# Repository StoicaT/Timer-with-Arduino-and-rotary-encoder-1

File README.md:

# Timer-with-rotary-encoder 
This countdown timer allows timings in the 1-9999 seconds range.
It is built around an Arduino Nano and timer programming is done with a rotary encoder.
The display of the duration of the delay and the remaining time is made with LCD display type 1602.

Programming:  Set number seconds (rotary encoder) - push - secondsX10 - push - 100Xseconds - push - 1000Xseconds
Now the time is set.
The next push will trigger the delay.

During the time delay the load will be powered through the Rel relay.
If the MEM button is pressed, no further programming is required, the previous value is retained.
More to https://www.instructables.com/id/Timer-With-Arduino-and-Rotary-Encoder/

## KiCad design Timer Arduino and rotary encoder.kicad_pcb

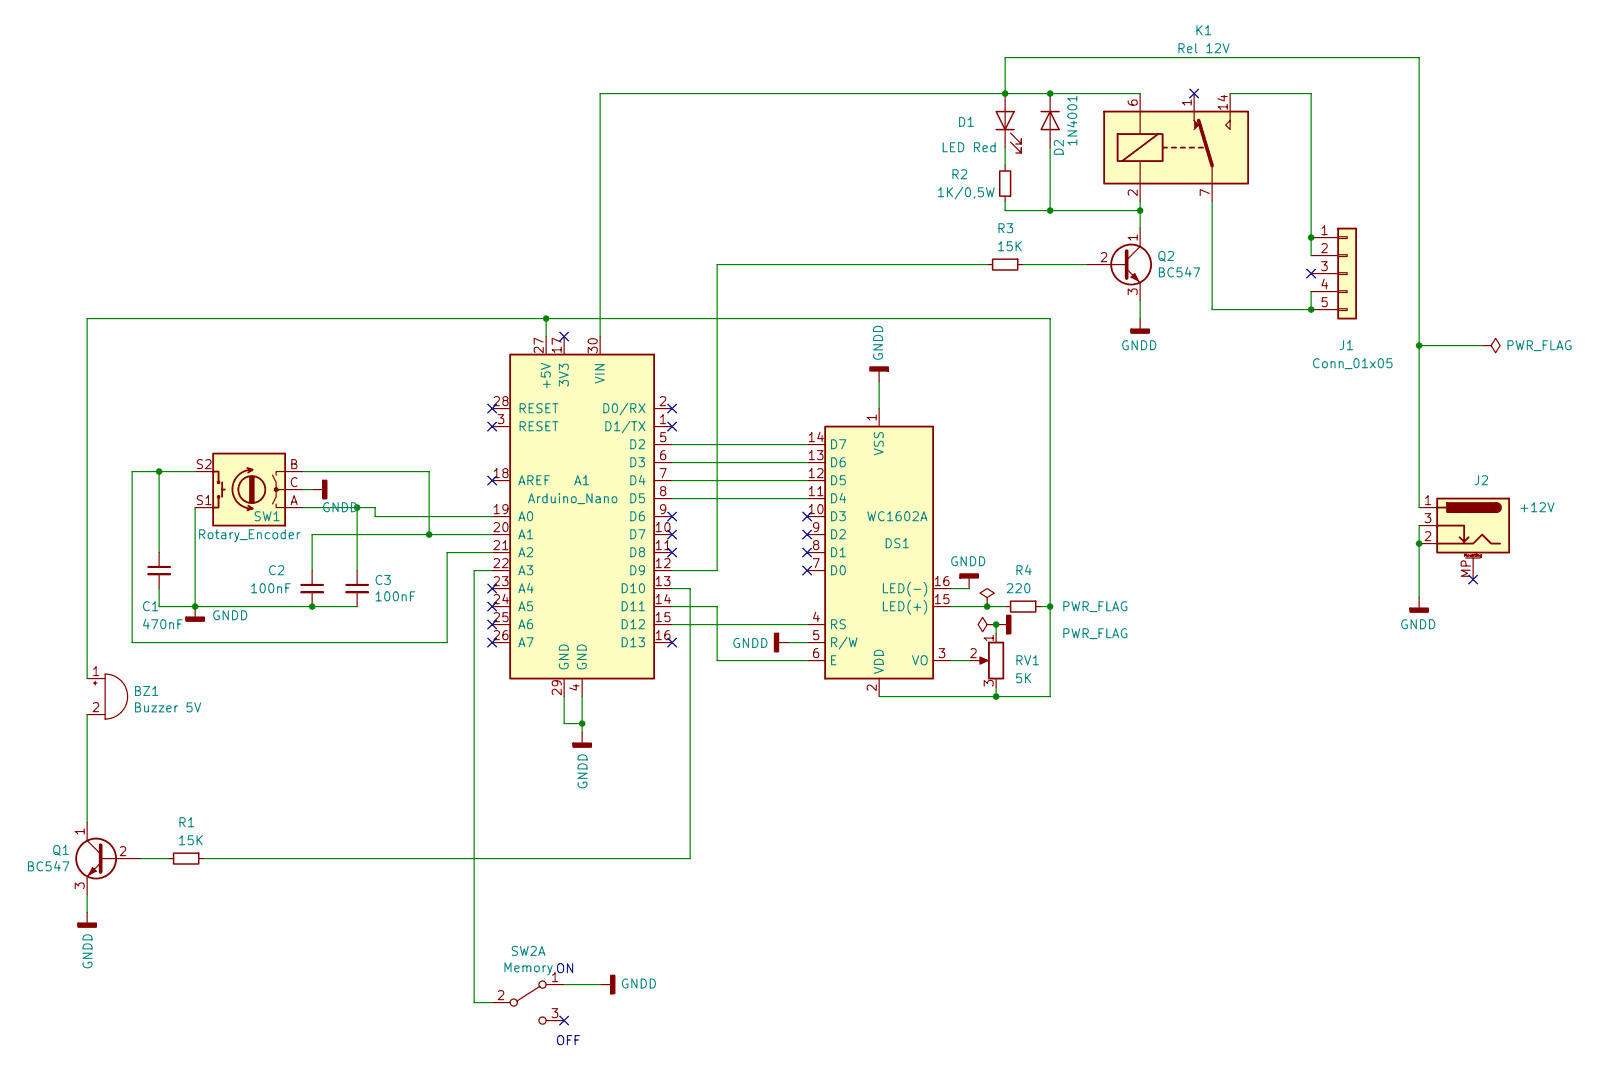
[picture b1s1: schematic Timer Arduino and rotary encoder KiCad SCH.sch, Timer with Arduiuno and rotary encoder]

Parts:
A1: Arduino_Nano; Arduino_Nano_WithMountingHoles
BZ1: Buzzer 5V; Buzzer_12x9.5RM7.6
C1: 470nF; C_Rect_L7.0mm_W2.0mm_P5.00mm
C2, C3: 100nF; C_Rect_L7.0mm_W2.0mm_P5.00mm
D1: LED Red; LED_D5.0mm
D2: 1N4001; D_DO-41_SOD81_P10.16mm_Horizontal
DS1: WC1602A
J1: Conn_01x05; PinHeader_1x05_P2.54mm_Horizontal
J2: +12V; BarrelJack_Horizontal
K1: Rel 12V
Q1, Q2: BC547; TO-92_Inline
R1, R3: 15K; R_Axial_DIN0207_L6.3mm_D2.5mm_P10.16mm_Horizontal
R2: 1K/0,5W; R_Axial_DIN0309_L9.0mm_D3.2mm_P12.70mm_Horizontal
R4: 220; R_Axial_DIN0207_L6.3mm_D2.5mm_P10.16mm_Horizontal
RV1: 5K; Potentiometer_Piher_PT-10-V10_Vertical
SW1: Rotary_Encoder; RotaryEncoder_Alps_EC11E-Switch_Vertical_H20mm
SW2: Memory; SW_CuK_JS202011CQN_DPDT_Straight

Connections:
GNDD: A1.4 (GND), A1.29 (GND), C1.2, C2.2, C3.2, DS1.1 (VSS), DS1.5 (R/W), DS1.16 (LED(-)), J2.2, J2.3, Q1.3 (E), Q2.3 (E), RV1.1, SW1.C, SW1.S1, SW2.1 (A)
unnamed: A1.5 (D2), DS1.14 (D7)
unnamed: A1.6 (D3), DS1.13 (D6)
unnamed: A1.7 (D4), DS1.12 (D5)
unnamed: A1.8 (D5), DS1.11 (D4)
unnamed: A1.12 (D9), R3.2
unnamed: A1.13 (D10), R1.1
unnamed: A1.14 (D11), DS1.6 (E)
unnamed: A1.15 (D12), DS1.4 (RS)
unnamed: A1.19 (A0), C3.1, SW1.A
unnamed: A1.20 (A1), C2.1, SW1.B
unnamed: A1.21 (A2), C1.1, SW1.S2
unnamed: A1.22 (A3), SW2.2 (B)
unnamed: A1.27 (+5V), BZ1.1 (-), DS1.2 (VDD), R4.1, RV1.3
unnamed: A1.30 (VIN), D1.2 (A), D2.1 (K), J2.1, K1.6
unnamed: BZ1.2 (+), Q1.1 (C)
unnamed: D1.1 (K), R2.2
unnamed: D2.2 (A), K1.2, Q2.1 (C), R2.1
unnamed: DS1.3 (VO), RV1.2
unnamed: DS1.15 (LED(+)), R4.2
unnamed: J1.1, J1.2, K1.14
unnamed: J1.4, J1.5, K1.7, K1.8
unnamed: Q1.2 (B), R1.2
unnamed: Q2.2 (B), R3.1

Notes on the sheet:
OFF

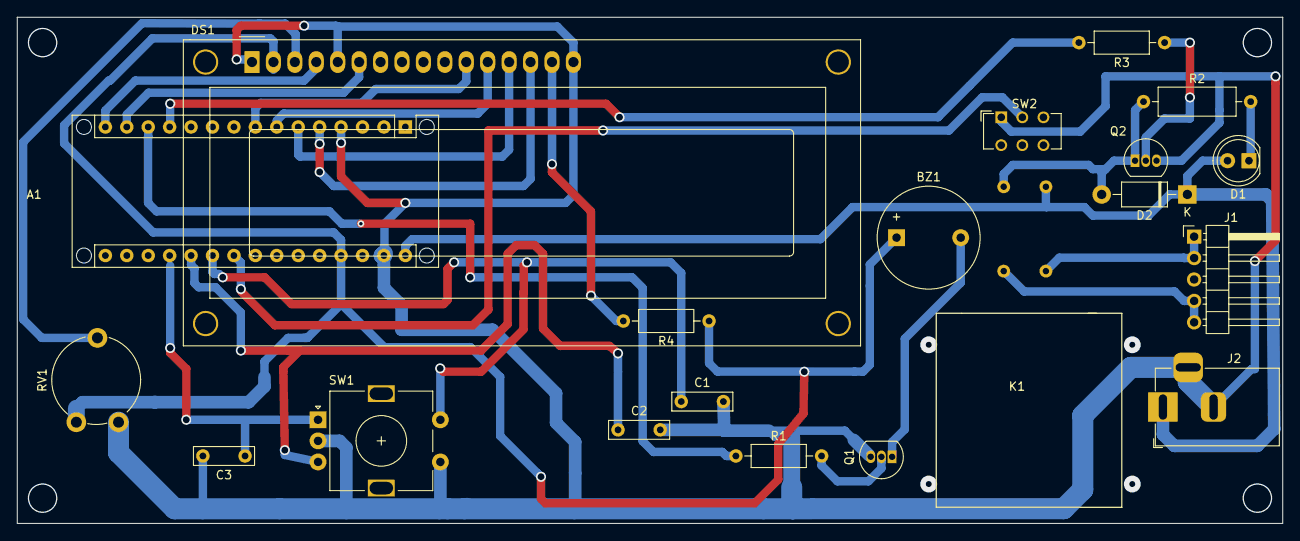
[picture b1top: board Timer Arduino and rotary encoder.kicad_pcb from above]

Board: 2 copper layers, 150.0 x 60.0 mm, 20 parts (0 on the bottom side), 24 nets.
